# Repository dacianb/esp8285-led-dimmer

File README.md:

# esp8285-led-dimmer
A basic ESP8285 LED Dimmer that has three channel mosfet output and can be used with 12V LED strips.

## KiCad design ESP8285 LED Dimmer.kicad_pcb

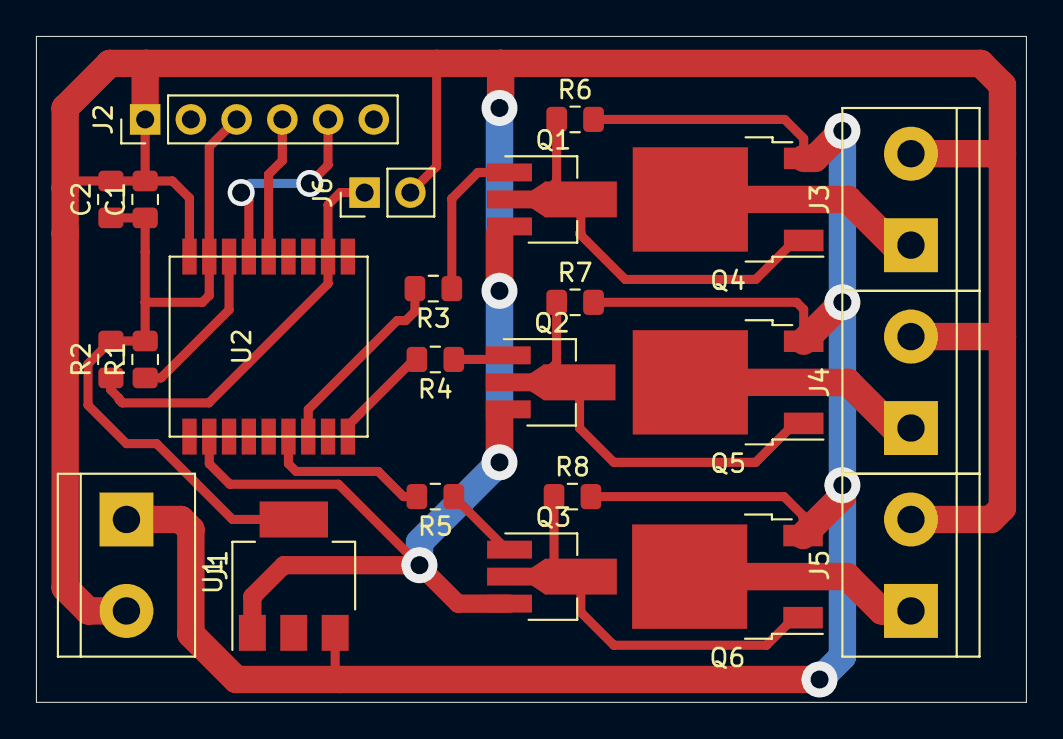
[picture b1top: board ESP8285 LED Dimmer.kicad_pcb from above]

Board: 2 copper layers, 55.0 x 37.0 mm, 24 parts (0 on the bottom side), 19 nets.

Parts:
C1: 100n; C_0805_2012Metric_Pad1.15x1.40mm_HandSolder
C2: 10u; C_0805_2012Metric_Pad1.15x1.40mm_HandSolder
J1, J3, J4, J5: Screw_Terminal_01x02; TerminalBlock_bornier-2_P5.08mm
J2: Conn_01x06; PinHeader_1x06_P2.54mm_Vertical
J6: Conn_01x02; PinHeader_1x02_P2.54mm_Vertical
Q1, Q2, Q3: Q_NPN_BCE; SOT-89-3_Handsoldering
Q4, Q5, Q6: IRFR9024; TO-252-alt
R1, R2, R6, R7, R8: 10k; R_0805_2012Metric_Pad1.15x1.40mm_HandSolder
R3, R4, R5: 4k7; R_0805_2012Metric_Pad1.15x1.40mm_HandSolder
U1: AMS1117-3.3; SOT-223-3_TabPin2
U2: ESP-01F; Ai-Thinker-ESP-01F

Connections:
+12V: J1.1, Q4.1, Q5.1, Q6.1, R6.2, R7.2, R8.2, U1.3
BootEN: J6.1, R2.1, U2.17
GND: C1.2, C2.2, J1.2, J2.1, J3.2, J4.2, J5.2, J6.2, Q1.3, Q2.3, Q3.3, U1.1, U2.2, U2.10
LED-OUT1: J3.1, Q4.3
LED-OUT2: J4.1, Q5.3
LED-OUT3: J5.1, Q6.3
unnamed: Q1.1, R3.1
unnamed: Q1.2, Q4.2, R6.1
unnamed: Q2.1, R4.1
unnamed: Q2.2, Q5.2, R7.1
unnamed: Q3.1, R5.1
unnamed: Q3.2, Q6.2, R8.1
PWM0: R3.2, U2.7
PWM1: R4.2, U2.9
PWM2: R5.2, U2.6
RST: R1.1, U2.12
RX: J2.5, U2.13
TX: J2.4, U2.14
VCC: C1.1, C2.1, J2.3, R1.2, R2.2, U1.2, U2.11

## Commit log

2019-10-20 Add some more ignore stuff
